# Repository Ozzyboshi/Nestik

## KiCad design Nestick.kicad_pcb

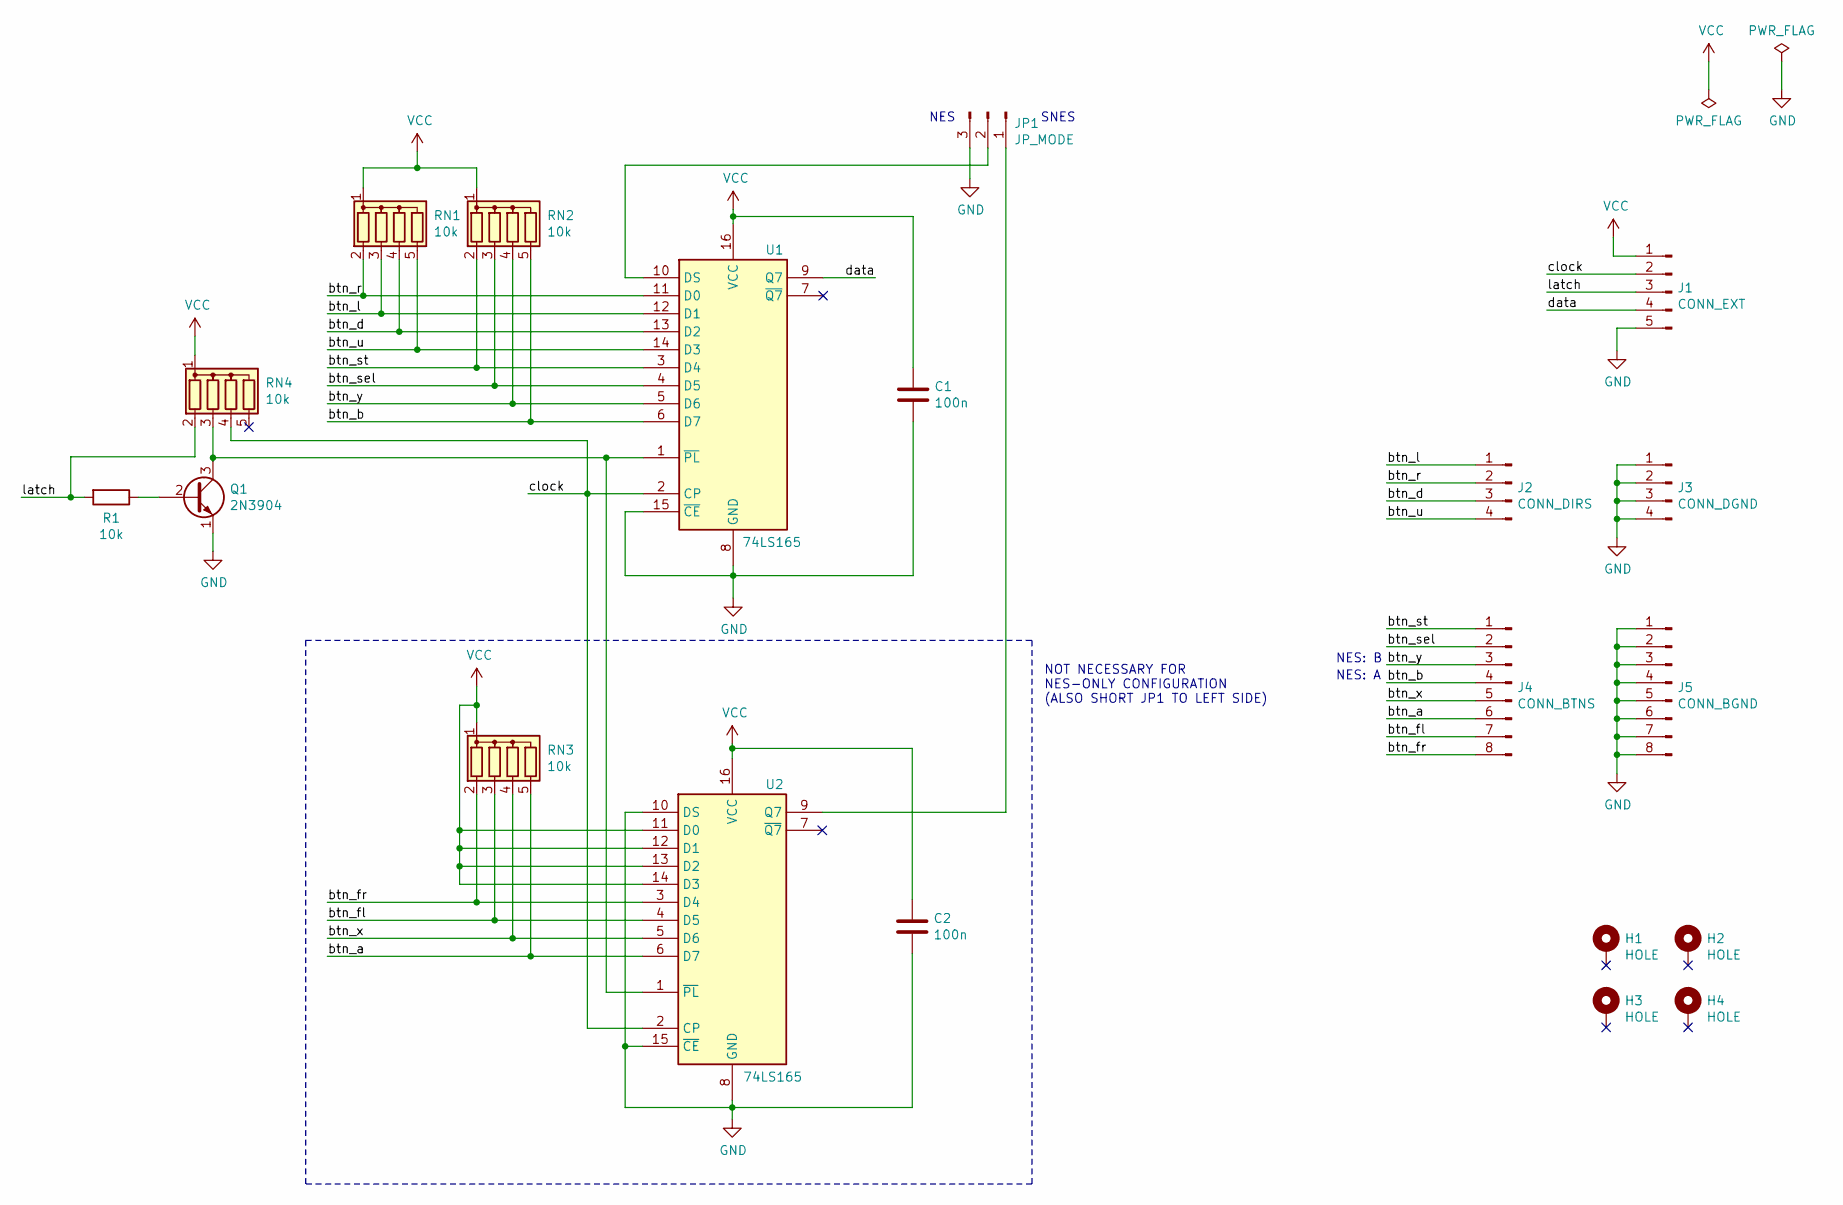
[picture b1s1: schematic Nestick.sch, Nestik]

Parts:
C1, C2: 100n; C_Disc_D7.0mm_W2.5mm_P5.00mm
H1, H2, H3, H4: HOLE; MountingHole_3.2mm_M3_Pad
J1: CONN_EXT; PinHeader_1x05_P2.54mm_Vertical
J2: CONN_DIRS; PinHeader_1x04_P2.54mm_Vertical
J3: CONN_DGND; PinHeader_1x04_P2.54mm_Vertical
J4: CONN_BTNS; PinHeader_1x08_P2.54mm_Vertical
J5: CONN_BGND; PinHeader_1x08_P2.54mm_Vertical
JP1: JP_MODE; PinHeader_1x03_P2.54mm_Vertical
Q1: 2N3904; TO-92_Inline
R1: 10k; R_Axial_DIN0207_L6.3mm_D2.5mm_P10.16mm_Horizontal
RN1, RN2, RN3, RN4: 10k; R_Array_SIP5
U1, U2: 74LS165; DIP-16_W7.62mm_Socket_LongPads

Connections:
/btn_a: J4.6, RN3.5 (R4), U2.6 (D7)
/btn_b: J4.4, RN2.5 (R4), U1.6 (D7)
/btn_d: J2.3, RN1.4 (R3), U1.13 (D2)
/btn_fl: J4.7, RN3.3 (R2), U2.4 (D5)
/btn_fr: J4.8, RN3.2 (R1), U2.3 (D4)
/btn_l: J2.1, RN1.3 (R2), U1.12 (D1)
/btn_r: J2.2, RN1.2 (R1), U1.11 (D0)
/btn_sel: J4.2, RN2.3 (R2), U1.4 (D5)
/btn_st: J4.1, RN2.2 (R1), U1.3 (D4)
/btn_u: J2.4, RN1.5 (R4), U1.14 (D3)
/btn_x: J4.5, RN3.4 (R3), U2.5 (D6)
/btn_y: J4.3, RN2.4 (R3), U1.5 (D6)
/clock: J1.2, RN4.4 (R3), U1.2 (CP), U2.2 (CP)
/data: J1.4, U1.9 (Q7)
/latch: J1.3, R1.2, RN4.2 (R1)
GND: C1.2, C2.2, J1.5, J3.1, J3.2, J3.3, J3.4, J5.1, J5.2, J5.3, J5.4, J5.5, J5.6, J5.7, J5.8, JP1.3, Q1.1 (E), U1.8 (GND), U1.15 (~CE), U2.8 (GND), U2.10 (DS), U2.15 (~CE)
unnamed: JP1.1, U2.9 (Q7)
unnamed: JP1.2, U1.10 (DS)
unnamed: Q1.2 (B), R1.1
unnamed: Q1.3 (C), RN4.3 (R2), U1.1 (~PL), U2.1 (~PL)
VCC: C1.1, C2.1, J1.1, RN1.1 (common), RN2.1 (common), RN3.1 (common), RN4.1 (common), U1.16 (VCC), U2.11 (D0), U2.12 (D1), U2.13 (D2), U2.14 (D3), U2.16 (VCC)

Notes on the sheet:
NES
SNES
NES: B
NES: A
NOT NECESSARY FOR NES-ONLY CONFIGURATION (ALSO SHORT JP1 TO LEFT SIDE)

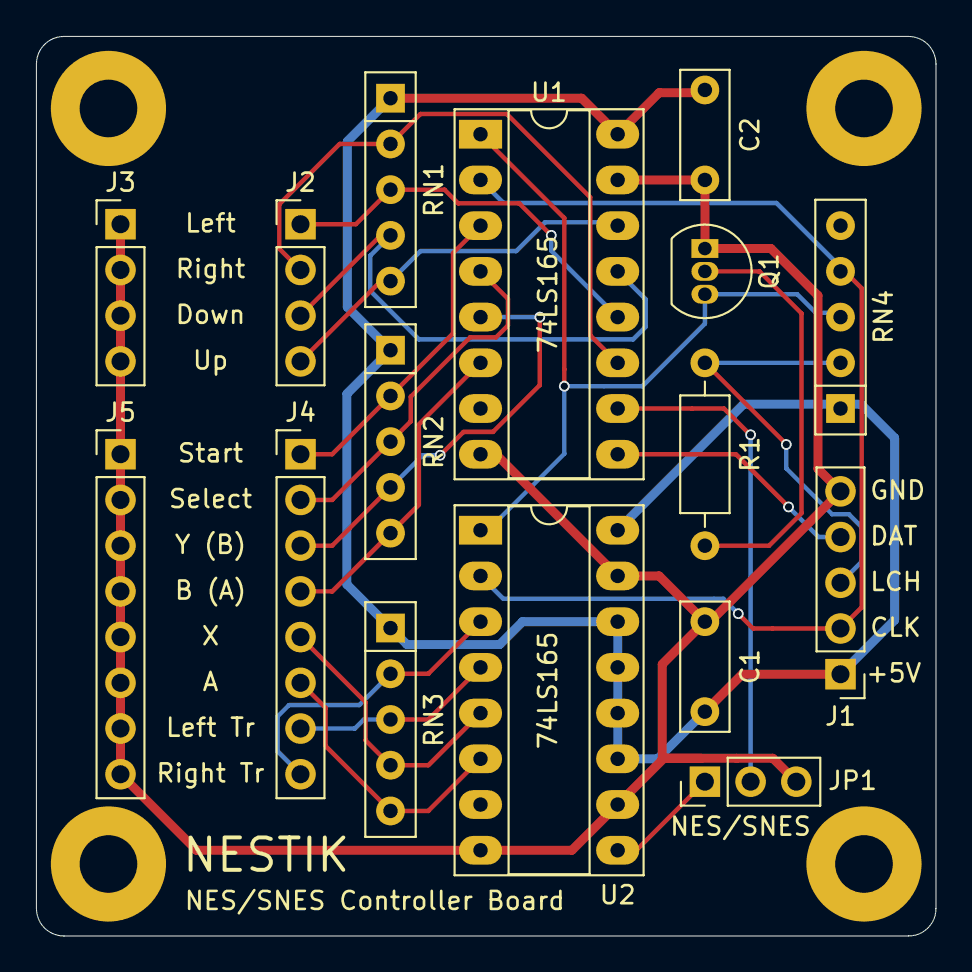
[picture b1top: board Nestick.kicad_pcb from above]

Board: 2 copper layers, 50.0 x 50.0 mm, 20 parts (0 on the bottom side), 21 nets.

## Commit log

2021-06-09 Dress up for release
2021-06-09 Back to 50x50mm
